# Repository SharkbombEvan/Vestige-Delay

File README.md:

This repository contains files for the Sharkbomb Audio Vestige delay. The Vestige delay is a combination of modulated delay and Echoplex-style JFET pream. 

Provided are the KiCad files, JLCPCB Gerber files, and Assembly files for JLCPCB Assembly.

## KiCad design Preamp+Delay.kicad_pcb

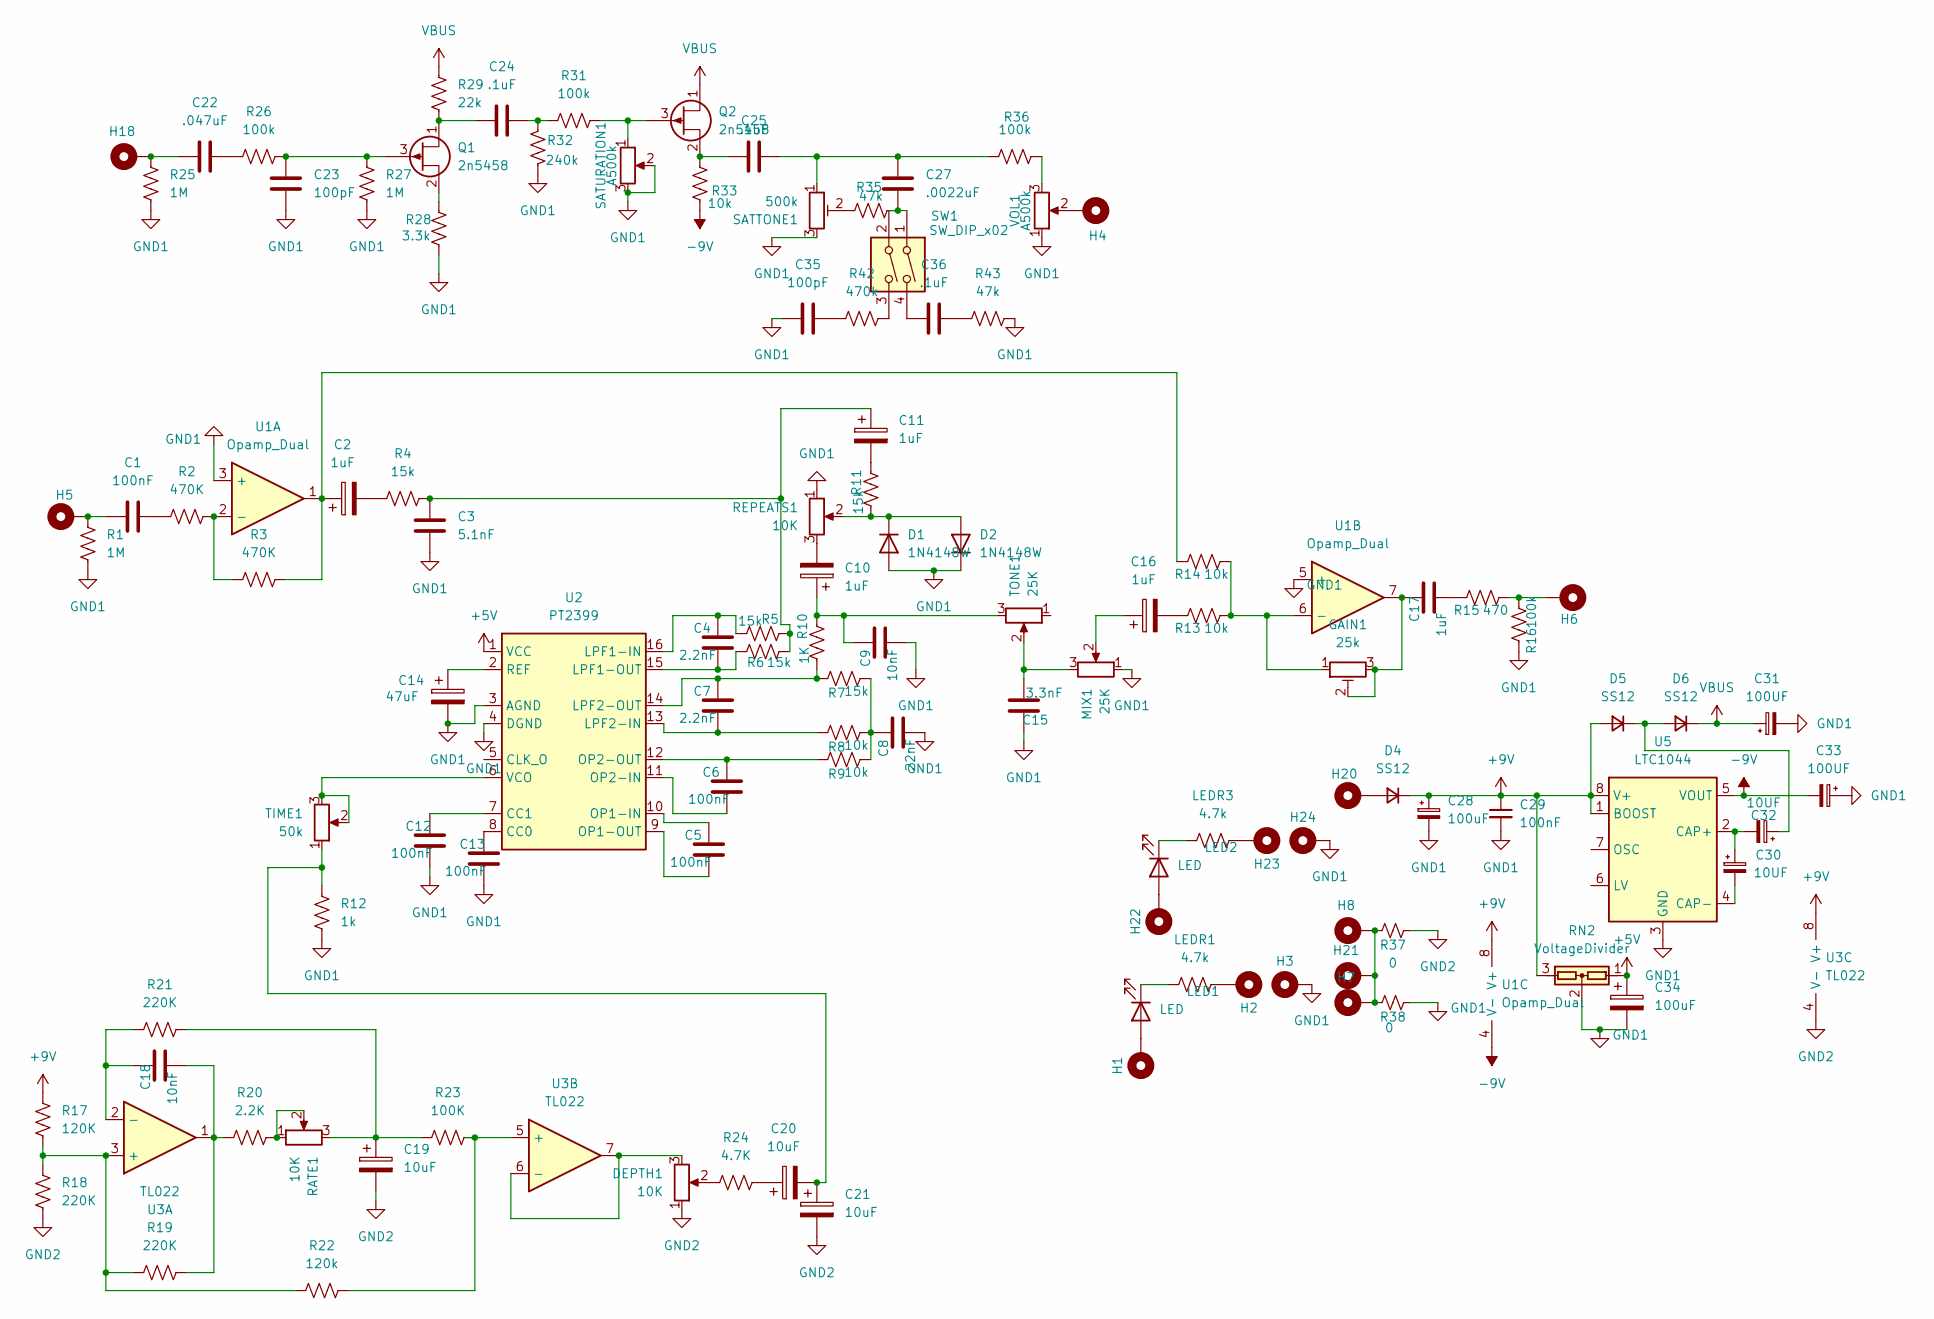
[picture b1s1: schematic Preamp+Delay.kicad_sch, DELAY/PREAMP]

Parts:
C1, C5, C6, C12, C13, C29: 100nF; C_0805_2012Metric
C2, C10, C11, C16, C17: 1uF; C_1206_3216Metric
C3: 5.1nF; C_0805_2012Metric
C4, C7: 2.2nF; C_0805_2012Metric
C8: 22nF; C_0805_2012Metric
C9, C18: 10nF; C_0805_2012Metric
C14: 47uF; CP_Radial_D5.0mm_P2.50mm
C15: 3.3nF; C_0805_2012Metric
C19, C20, C21: 10uF; C_1206_3216Metric
C22: .047uF; C_0805_2012Metric
C23, C35: 100pF; C_0805_2012Metric
C24, C25, C36: .1uF; C_0805_2012Metric
C27: .0022uF; C_0805_2012Metric
C28, C34: 100uF; CP_Radial_D5.0mm_P2.50mm
C30, C32: 10UF; CP_Radial_D5.0mm_P2.50mm
C31, C33: 100UF; CP_Radial_D5.0mm_P2.50mm
D1, D2: 1N4148W; Nexperia_CFP3_SOD-123W
D4, D5, D6: SS12; D_SOD-123
DEPTH1: 10K; 16mm Pot
GAIN1: 25k; TaydaTrimmer
H1, H2, H3, H4, H5, H6, H7, H8, H18, H20, H21, H22, H23, H24: MountingHole_Pad; 2.0mm Pad
LED1, LED2: LED; LED_D3.0mm_Clear
LEDR1, LEDR3: 4.7k; R_0805_2012Metric
MIX1: 25K; 16mm Pot
Q1, Q2: 2n5458; TO-92L_Inline_Wide
R1, R25, R27: 1M; R_0805_2012Metric
R2, R3: 470K; R_0805_2012Metric
R4, R5, R6, R7, R11: 15k; R_0805_2012Metric
R8, R9, R13, R14, R33: 10k; R_0805_2012Metric
R10: 1K; R_0805_2012Metric
R12: 1k; R_0805_2012Metric
R15: 470; R_0805_2012Metric
R16, R26, R31, R36: 100k; R_0805_2012Metric
R17: 120K; R_0805_2012Metric
R18, R19, R21: 220K; R_0805_2012Metric
R20: 2.2K; R_0805_2012Metric
R22: 120k; R_0805_2012Metric
R23: 100K; R_0805_2012Metric
R24: 4.7K; R_0805_2012Metric
R28: 3.3k; R_0805_2012Metric
R29: 22k; R_0805_2012Metric
R32: 240k; R_0805_2012Metric
R35, R43: 47k; R_0805_2012Metric
R37, R38: 0; R_0805_2012Metric
R42: 470k; R_0805_2012Metric
RATE1: 10K; 16mm Pot
REPEATS1: 10K; 16mm Pot
RN2: VoltageDivider; TO-220-3_Vertical
SATTONE1: 500k; TaydaTrimmer
SATURATION1: A500k; 16mm Pot
SW1: SW_DIP_x02; SW_DIP_SPSTx02_Slide_6.7x6.64mm_W7.62mm_P2.54mm_LowProfile
TIME1: 50k; 16mm Pot
TONE1: 25K; 16mm Pot
U1: Opamp_Dual; DIP-8_W7.62mm
U2: PT2399; DIP-16_W7.62mm
U3: TL022; DIP-8_W7.62mm
U5: LTC1044; DIP-8_W7.62mm
VOL1: A500k; 16mm Pot

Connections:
+5V: C34.1, RN2.1, U2.1 (VCC)
+9V: C28.1, C29.1, D4.1 (K), D5.2 (A), R17.2, RN2.3, U1.8 (V+), U3.8 (V+), U5.1 (BOOST), U5.8 (V+)
-9V: C33.2, R33.1, U1.4 (V-), U5.5 (VOUT)
GND1: C3.1, C8.1, C9.1, C12.1, C13.1, C14.2, C15.2, C23.1, C28.2, C29.2, C31.2, C33.1, C34.2, C35.1, D1.2 (A), D2.1 (K), H3.1, H24.1, MIX1.1, R1.1, R12.2, R16.1, R25.2, R27.1, R28.1, R32.2, R38.2, R43.1, REPEATS1.1, RN2.2, SATTONE1.3, SATURATION1.2, SATURATION1.3, U1.3 (+), U1.5 (+), U2.3 (AGND), U2.4 (DGND), U5.3 (GND), VOL1.1
GND2: C19.2, C21.2, DEPTH1.1, R18.1, R37.2, U3.4 (V-)
unnamed: C1.1, H5.1, R1.2
unnamed: C1.2, R2.2
unnamed: C2.1, R3.1, R14.1, U1.1
unnamed: C2.2, R4.2
unnamed: C8.2, R7.2, R8.2, R9.2
unnamed: C9.2, C10.1, R10.1, TONE1.3
unnamed: C10.2, REPEATS1.3
unnamed: C3.2, C11.1, R4.1, R5.1, R6.2
unnamed: C11.2, R11.1
unnamed: C15.1, MIX1.3, TONE1.2
unnamed: C16.1, MIX1.2
unnamed: C16.2, R13.1
unnamed: C17.1, R15.1
unnamed: C17.2, GAIN1.2, GAIN1.3, U1.7
unnamed: C18.1, R19.2, R20.1, U3.1
unnamed: C19.1, R21.2, R23.1, RATE1.3
unnamed: C20.1, R24.2
unnamed: C20.2, C21.1, R12.1, TIME1.1
unnamed: C22.1, H18.1, R25.1
unnamed: C22.2, R26.1
unnamed: C24.1, R31.2, R32.1
unnamed: C25.1, C27.1, R36.2, SATTONE1.1
unnamed: C27.2, R35.1, SW1.1, SW1.2
unnamed: C35.2, R42.2
unnamed: C36.1, SW1.4
unnamed: C36.2, R43.2
unnamed: D1.1 (K), D2.2 (A), R11.2, REPEATS1.2
unnamed: D4.2 (A), H20.1
unnamed: C32.1, D5.1 (K), D6.2 (A)
unnamed: DEPTH1.2, R24.1
unnamed: H2.1, LEDR1.2
unnamed: H4.1, VOL1.2
unnamed: H6.1, R15.2, R16.2
unnamed: H7.1, H8.1, H21.1, R37.1, R38.1
unnamed: H23.1, LEDR3.2
unnamed: H1.1, LED1.2 (A)
unnamed: LED1.1 (K), LEDR1.1
unnamed: H22.1, LED2.2 (A)
unnamed: LED2.1 (K), LEDR3.1
unnamed: C24.2, Q1.1 (D), R29.1
unnamed: C23.2, Q1.3 (G), R26.2, R27.2
unnamed: Q1.2 (S), R28.2
unnamed 47: Q2.3 (G), R31.1, SATURATION1.1; also elsewhere on the board
unnamed: C25.2, Q2.2 (S), R33.2
unnamed: R20.2, RATE1.1, RATE1.2
unnamed: R35.2, SATTONE1.2
unnamed: R36.1, VOL1.3
unnamed: R42.1, SW1.3
unnamed: R2.1, R3.2, U1.2 (-)
unnamed: GAIN1.1, R13.2, R14.2, U1.6 (-)
unnamed: C13.2, U2.8 (CC0)
unnamed: C12.2, U2.7 (CC1)
unnamed: C4.2, R5.2, U2.16 (LPF1-IN)
unnamed: C4.1, R6.1, U2.15 (LPF1-OUT)
unnamed: C7.1, R8.1, U2.13 (LPF2-IN)
unnamed: C7.2, R7.1, R10.2, U2.14 (LPF2-OUT)
unnamed: C5.2, U2.10 (OP1-IN)
unnamed: C5.1, U2.9 (OP1-OUT)
unnamed: C6.1, U2.11 (OP2-IN)
unnamed: C6.2, R9.1, U2.12 (OP2-OUT)
unnamed: C14.1, U2.2 (REF)
unnamed: TIME1.2, TIME1.3, U2.6 (VCO)
unnamed: R17.1, R18.2, R19.1, R22.1, U3.3 (+)
unnamed: C18.2, R21.1, U3.2 (-)
unnamed: R22.2, R23.2, U3.5 (+)
unnamed: DEPTH1.3, U3.6 (-), U3.7
unnamed: C30.1, C32.2, U5.2 (CAP+)
unnamed: C30.2, U5.4 (CAP-)
VBUS: C31.1, D6.1 (K), Q2.1 (D), R29.2

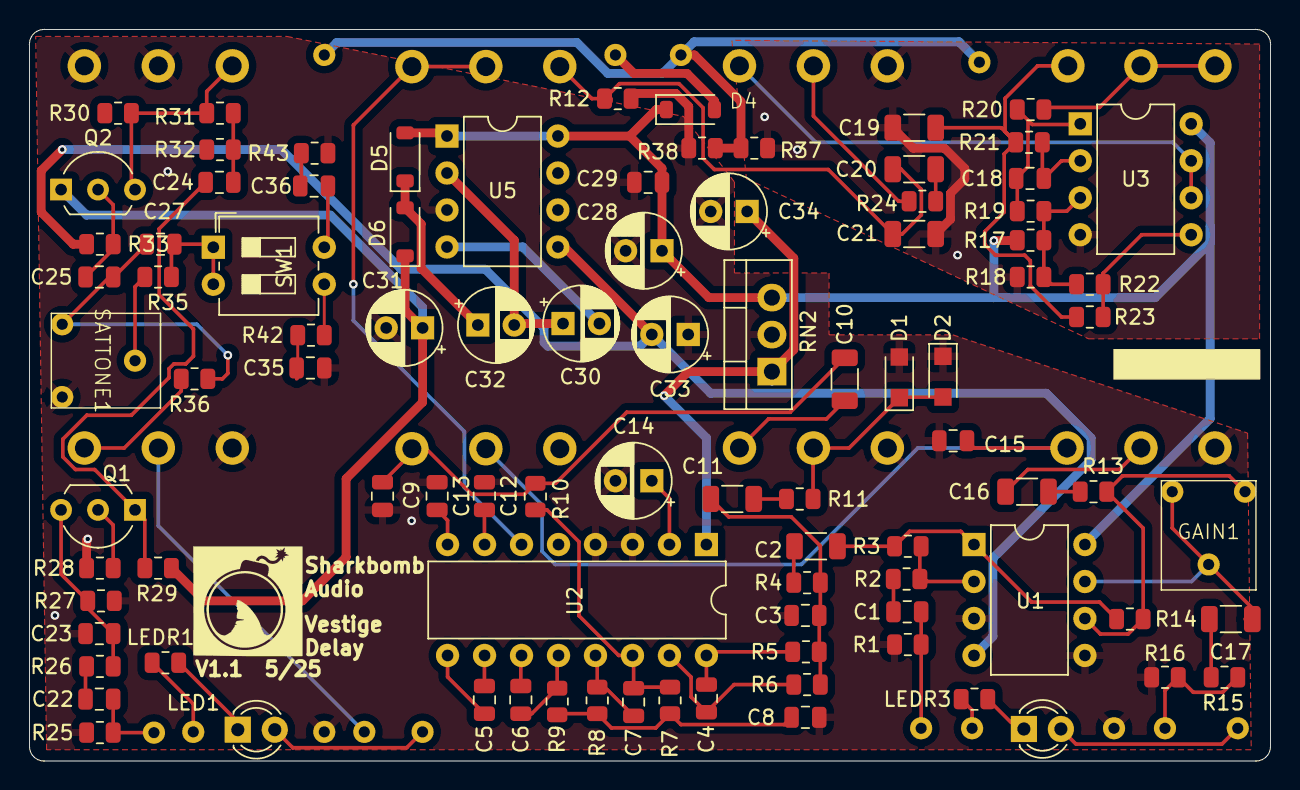
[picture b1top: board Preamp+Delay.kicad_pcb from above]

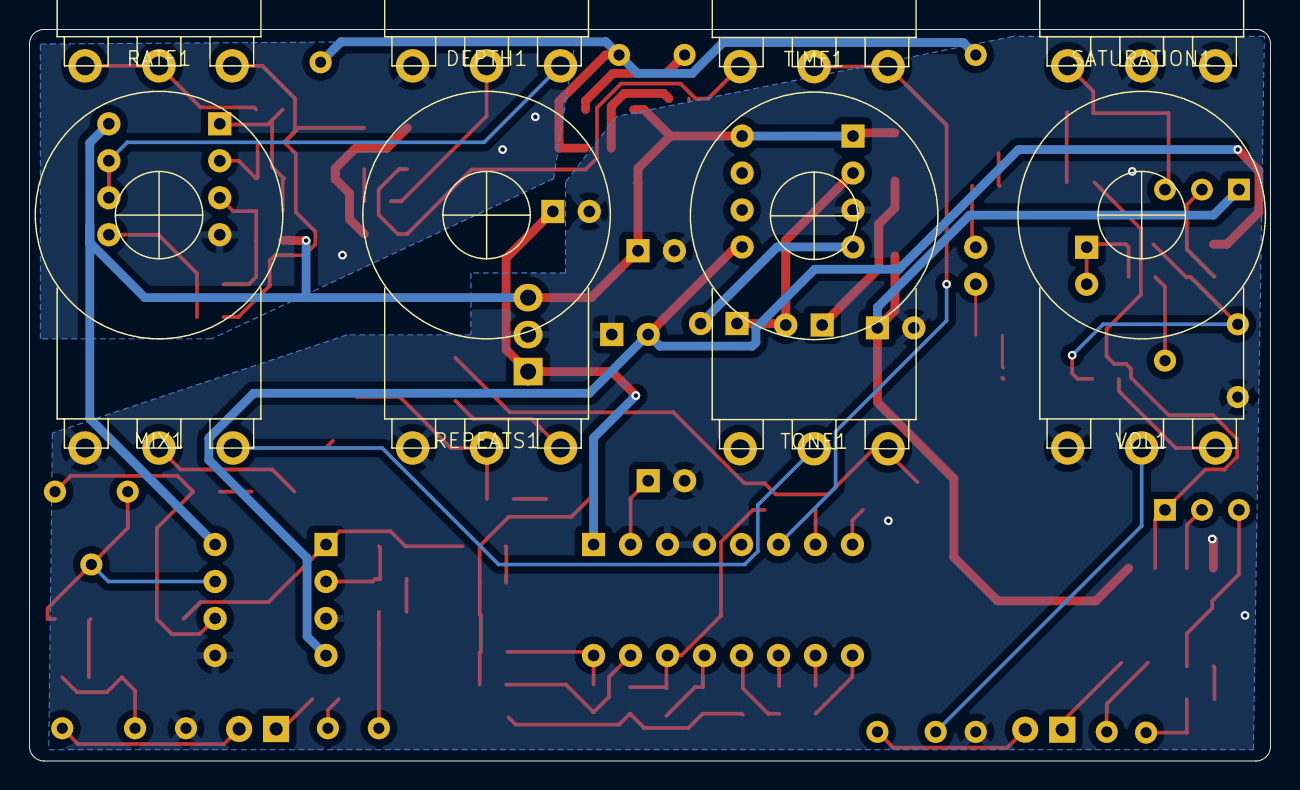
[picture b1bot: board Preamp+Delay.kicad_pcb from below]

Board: 2 copper layers, 85.2 x 50.2 mm, 115 parts (8 on the bottom side), 74 nets.

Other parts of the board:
R30: 100k; R_0805_2012Metric

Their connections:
unnamed 47: R30.2; also elsewhere on the board

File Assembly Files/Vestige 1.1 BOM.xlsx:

Reference | Value | Footprint | Qty
C1,C5,C6,C12,C13,C29 | 100nF | Capacitor_SMD:C_0805_2012Metric | 6.0
C2,C10,C11,C16,C17 | 1uF | Capacitor_SMD:C_1206_3216Metric | 5.0
C3 | 5.1nF | Capacitor_SMD:C_0805_2012Metric | 1.0
C4,C7 | 2.2nF | Capacitor_SMD:C_0805_2012Metric | 2.0
C8 | 22nF | Capacitor_SMD:C_0805_2012Metric | 1.0
C9,C18 | 10nF | Capacitor_SMD:C_0805_2012Metric | 2.0
C14 | 47uF | Capacitor_THT:CP_Radial_D5.0mm_P2.50mm | 1.0
C15 | 3.3nF | Capacitor_SMD:C_0805_2012Metric | 1.0
C19,C20,C21 | 10uF | Capacitor_SMD:C_1206_3216Metric | 3.0
C22 | .047uF | Capacitor_SMD:C_0805_2012Metric | 1.0
C23,C35 | 100pF | Capacitor_SMD:C_0805_2012Metric | 2.0
C24,C25,C36 | .1uF | Capacitor_SMD:C_0805_2012Metric | 3.0
C27 | .0022uF | Capacitor_SMD:C_0805_2012Metric | 1.0
D1,D2 | 1N4148W | Diode_SMD:Nexperia_CFP3_SOD-123W | 2.0
D4,D5,D6 | SS12 | Diode_SMD:D_SOD-123 | 3.0
LEDR1,LEDR3 | 4.7k | Resistor_SMD:R_0805_2012Metric | 2.0
R1,R25,R27 | 1M | Resistor_SMD:R_0805_2012Metric | 3.0
R2,R3 | 470K | Resistor_SMD:R_0805_2012Metric | 2.0
R4,R5,R6,R7,R11 | 15k | Resistor_SMD:R_0805_2012Metric | 5.0
R8,R9,R13,R14,R33 | 10k | Resistor_SMD:R_0805_2012Metric | 5.0
R10 | 1K | Resistor_SMD:R_0805_2012Metric | 1.0
R12 | 1k | Resistor_SMD:R_0805_2012Metric | 1.0
R15 | 470.0 | Resistor_SMD:R_0805_2012Metric | 1.0
R16,R26,R31,R36 | 100k | Resistor_SMD:R_0805_2012Metric | 4.0
R17 | 120K | Resistor_SMD:R_0805_2012Metric | 1.0
R18,R19,R21 | 220K | Resistor_SMD:R_0805_2012Metric | 3.0
R20 | 2.2K | Resistor_SMD:R_0805_2012Metric | 1.0
R22 | 120k | Resistor_SMD:R_0805_2012Metric | 1.0
R23 | 100K | Resistor_SMD:R_0805_2012Metric | 1.0
R24 | 4.7K | Resistor_SMD:R_0805_2012Metric | 1.0
R28 | 3.3k | Resistor_SMD:R_0805_2012Metric | 1.0
R29 | 22k | Resistor_SMD:R_0805_2012Metric | 1.0
R32 | 240k | Resistor_SMD:R_0805_2012Metric | 1.0
R35,R43 | 47k | Resistor_SMD:R_0805_2012Metric | 2.0
R37,R38 | 0.0 | Resistor_SMD:R_0805_2012Metric | 2.0
R42 | 470k | Resistor_SMD:R_0805_2012Metric | 1.0
SATTONE1 | 500k | GuitarPedalParts:TaydaTrimmer | 1.0
SATURATION1,VOL1 | A500k | GuitarPedalParts:16mm Pot | 2.0
